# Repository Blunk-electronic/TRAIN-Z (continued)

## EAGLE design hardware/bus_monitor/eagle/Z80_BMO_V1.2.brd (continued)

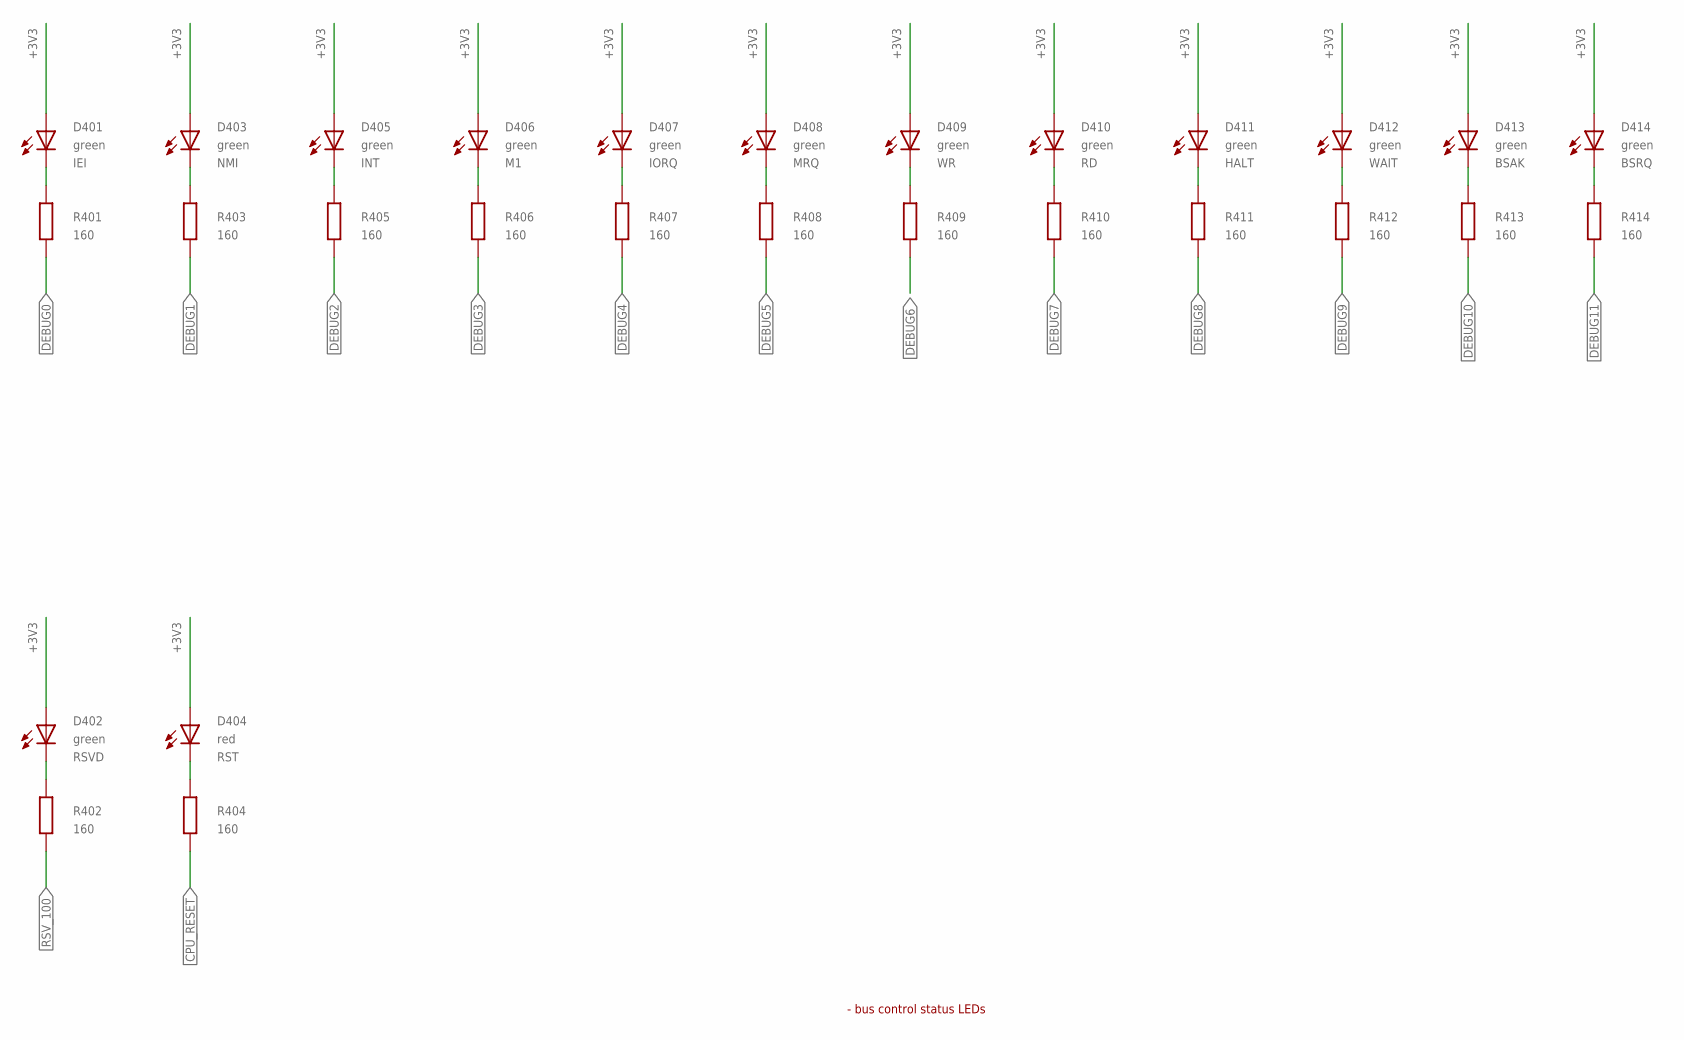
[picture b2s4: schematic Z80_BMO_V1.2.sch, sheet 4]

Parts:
D401, D402, D403, D405, D406, D407, D408, D409, D410, D411, D412, D413, D414: green; T_LED_3MM; PART_CODE_BEL LED_PAC_T_3mm_VAL_green
D404: red; T_LED_3MM; PART_CODE_BEL LED_PAC_T_3mm_VAL_red
R401, R402, R403, R404, R405, R406, R407, R408, R409, R410, R411, R412, R413, R414: 160; T_0207_GRID10MM; PART_CODE_BEL R_PAC_T_0207_GRID10mm_VAL_160

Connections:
!CPU_RESET: R404.2; also elsewhere on the board
+3V3: D401.A, D402.A, D403.A, D404.A, D405.A, D406.A, D407.A, D408.A, D409.A, D410.A, D411.A, D412.A, D413.A, D414.A; also elsewhere on the board
DEBUG0: R401.2; also elsewhere on the board
DEBUG0_LED: D401.C, R401.1
DEBUG1: R403.2; also elsewhere on the board
DEBUG1_LED: D403.C, R403.1
DEBUG2: R405.2; also elsewhere on the board
DEBUG2_LED: D405.C, R405.1
DEBUG3: R406.2; also elsewhere on the board
DEBUG3_LED: D406.C, R406.1
DEBUG4: R407.2; also elsewhere on the board
DEBUG4_LED: D407.C, R407.1
DEBUG5: R408.2; also elsewhere on the board
DEBUG5_LED: D408.C, R408.1
DEBUG6: R409.2; also elsewhere on the board
DEBUG6_LED: D409.C, R409.1
DEBUG7: R410.2; also elsewhere on the board
DEBUG7_LED: D410.C, R410.1
DEBUG8: R411.2; also elsewhere on the board
DEBUG8_LED: D411.C, R411.1
DEBUG9: R412.2; also elsewhere on the board
DEBUG9_LED: D412.C, R412.1
DEBUG10: R413.2; also elsewhere on the board
DEBUG10_LED: D413.C, R413.1
DEBUG11: R414.2; also elsewhere on the board
DEBUG11_LED: D414.C, R414.1
RST_LED_C: D404.C, R404.1
RSV_100: R402.2; also elsewhere on the board
RSV_100_LED: D402.C, R402.1

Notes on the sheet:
- bus control status LEDs

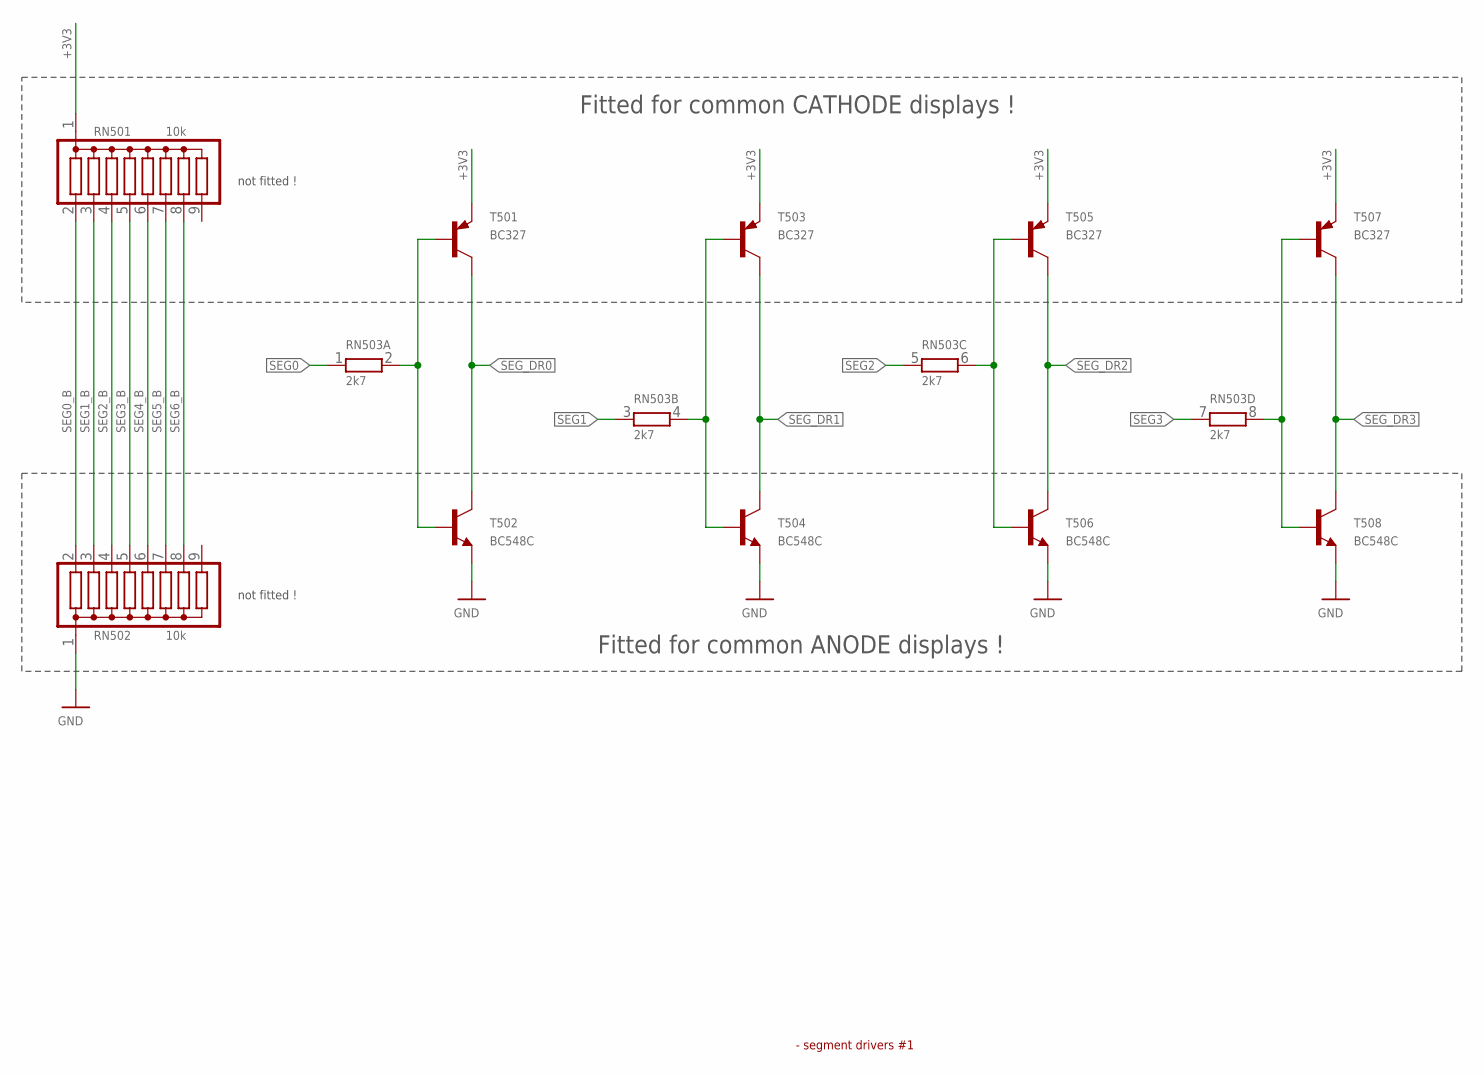
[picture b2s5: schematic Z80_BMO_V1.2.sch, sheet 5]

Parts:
RN501, RN502: 10k; T_SIL9; PART_CODE_BEL RN_PAC_T_SIL9_VAL_10k
RN503: 2k7; T_SIL8; PART_CODE_BEL RN_PAC_T_SIL8_VAL_2k7
T501, T503, T505, T507: BC327; T_TO92-CBE; PART_CODE_BEL T_PAC_T_TO92-CBE_VAL_BC327
T502, T504, T506, T508: BC548C; T_TO92-CBE; PART_CODE_BEL T_PAC_T_TO92-CBE_VAL_BC548C

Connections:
+3V3: RN501.1, T501.E, T503.E, T505.E, T507.E; also elsewhere on the board
GND: RN502.1, T502.E, T504.E, T506.E, T508.E; also elsewhere on the board
SEG0: RN503.1; also elsewhere on the board
SEG0_B: RN501.2, RN502.2, RN503.2, T501.B, T502.B
SEG1: RN503.3 (1); also elsewhere on the board
SEG1_B: RN501.3, RN502.3, RN503.4 (2), T503.B, T504.B
SEG2: RN503.5 (1); also elsewhere on the board
SEG2_B: RN501.4, RN502.4, RN503.6 (2), T505.B, T506.B
SEG3: RN503.7 (1); also elsewhere on the board
SEG3_B: RN501.5, RN502.5, RN503.8 (2), T507.B, T508.B
SEG4_B: RN501.6, RN502.6; also elsewhere on the board
SEG5_B: RN501.7, RN502.7; also elsewhere on the board
SEG6_B: RN501.8, RN502.8; also elsewhere on the board
SEG_DR0: T501.C, T502.C; also elsewhere on the board
SEG_DR1: T503.C, T504.C; also elsewhere on the board
SEG_DR2: T505.C, T506.C; also elsewhere on the board
SEG_DR3: T507.C, T508.C; also elsewhere on the board

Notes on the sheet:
Fitted for common ANODE displays !
Fitted for common CATHODE displays !
not fitted !
- segment drivers #1

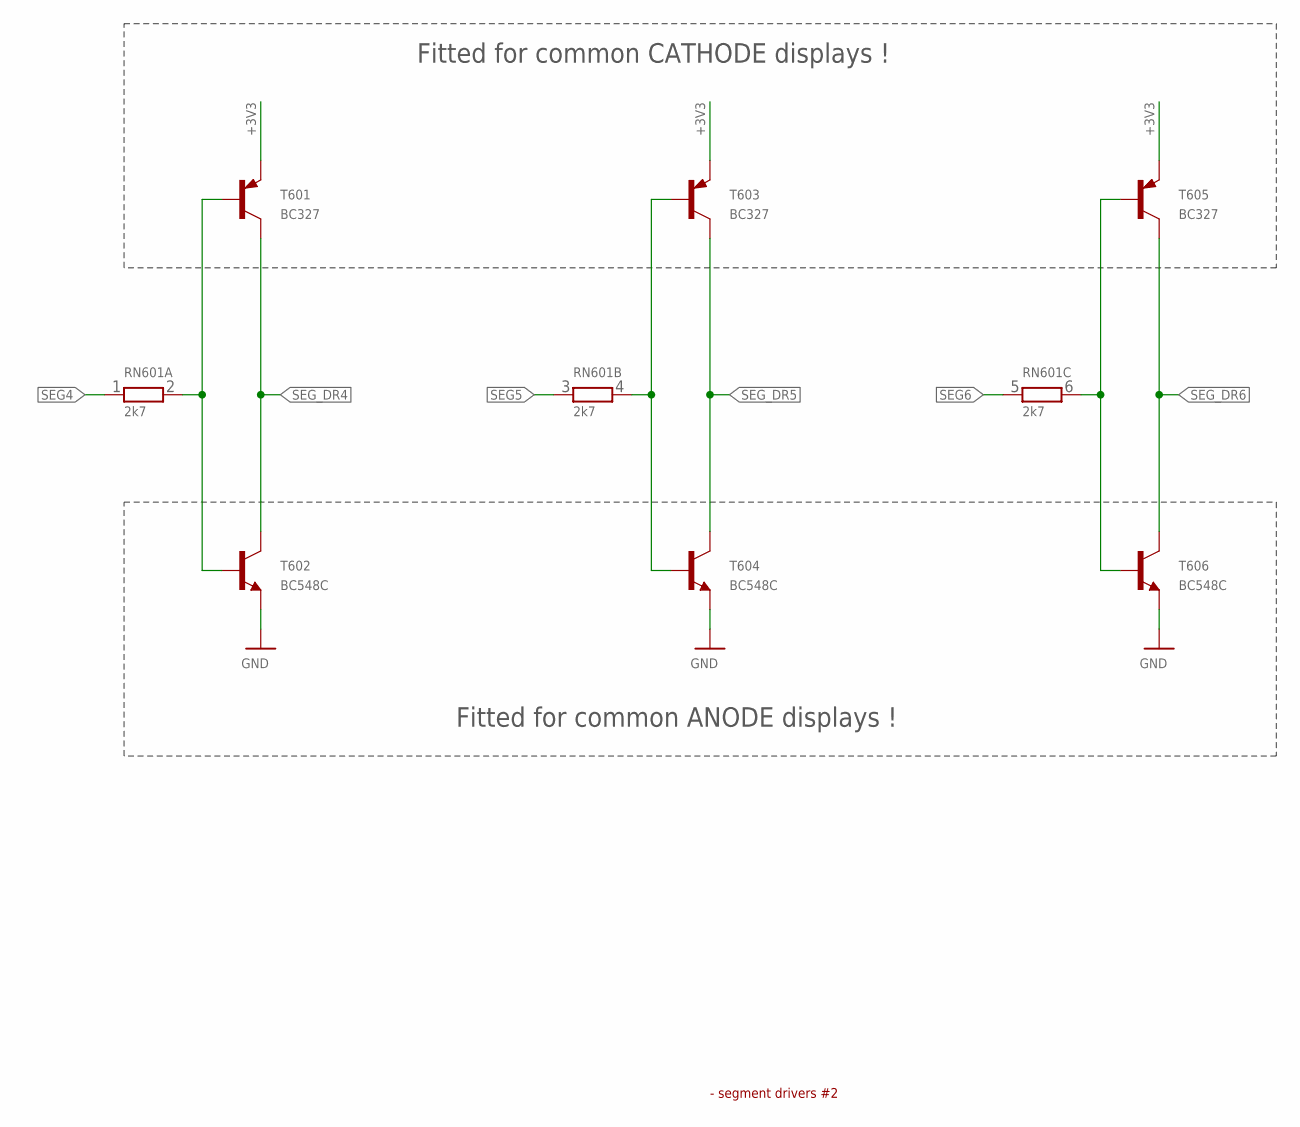
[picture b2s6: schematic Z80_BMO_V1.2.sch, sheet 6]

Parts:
RN601: 2k7; T_SIL8; PART_CODE_BEL RN_PAC_T_SIL8_VAL_2k7
T601, T603, T605: BC327; T_TO92-CBE; PART_CODE_BEL T_PAC_T_TO92-CBE_VAL_BC327
T602, T604, T606: BC548C; T_TO92-CBE; PART_CODE_BEL T_PAC_T_TO92-CBE_VAL_BC548C

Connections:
+3V3: T601.E, T603.E, T605.E; also elsewhere on the board
GND: T602.E, T604.E, T606.E; also elsewhere on the board
SEG4: RN601.1; also elsewhere on the board
SEG4_B: RN601.2, T601.B, T602.B; also elsewhere on the board
SEG5: RN601.3 (1); also elsewhere on the board
SEG5_B: RN601.4 (2), T603.B, T604.B; also elsewhere on the board
SEG6: RN601.5 (1); also elsewhere on the board
SEG6_B: RN601.6 (2), T605.B, T606.B; also elsewhere on the board
SEG_DR4: T601.C, T602.C; also elsewhere on the board
SEG_DR5: T603.C, T604.C; also elsewhere on the board
SEG_DR6: T605.C, T606.C; also elsewhere on the board

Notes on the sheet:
Fitted for common ANODE displays !
Fitted for common CATHODE displays !
- segment drivers #2

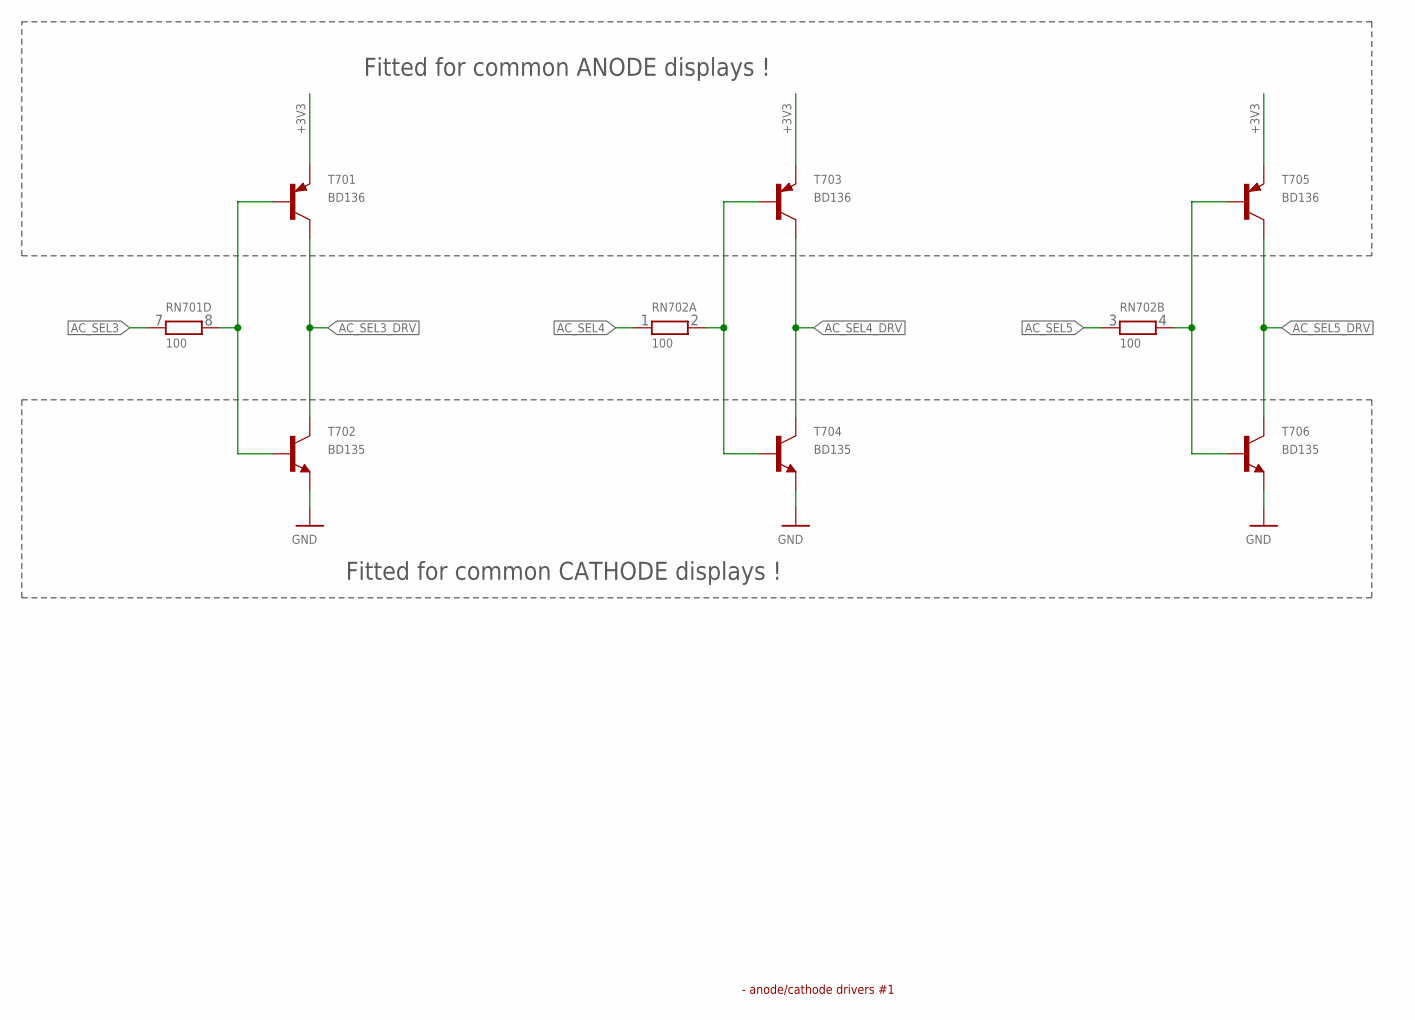
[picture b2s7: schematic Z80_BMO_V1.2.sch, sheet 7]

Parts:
RN701, RN702: 100; T_SIL8; PART_CODE_BEL RN_PAC_T_SIL8_VAL_100
T701, T703, T705: BD136; T_TO126_VERTICAL; PART_CODE_BEL T_PAC_T_TO126_VERTICAL_VAL_BD136
T702, T704, T706: BD135; T_TO126_VERTICAL; PART_CODE_BEL T_PAC_T_TO126_VERTICAL_VAL_BD135

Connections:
+3V3: T701.E, T703.E, T705.E; also elsewhere on the board
AC_SEL3: RN701.7 (1); also elsewhere on the board
AC_SEL3_DRV: T701.C, T702.C; also elsewhere on the board
AC_SEL4: RN702.1; also elsewhere on the board
AC_SEL4_DRV: T703.C, T704.C; also elsewhere on the board
AC_SEL5: RN702.3 (1); also elsewhere on the board
AC_SEL5_DRV: T705.C, T706.C; also elsewhere on the board
AC_SEL_B3: RN701.8 (2), T701.B, T702.B; also elsewhere on the board
AC_SEL_B4: RN702.2, T703.B, T704.B; also elsewhere on the board
AC_SEL_B5: RN702.4 (2), T705.B, T706.B; also elsewhere on the board
GND: T702.E, T704.E, T706.E; also elsewhere on the board

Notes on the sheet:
Fitted for common ANODE displays !
Fitted for common CATHODE displays !
- anode/cathode drivers #1

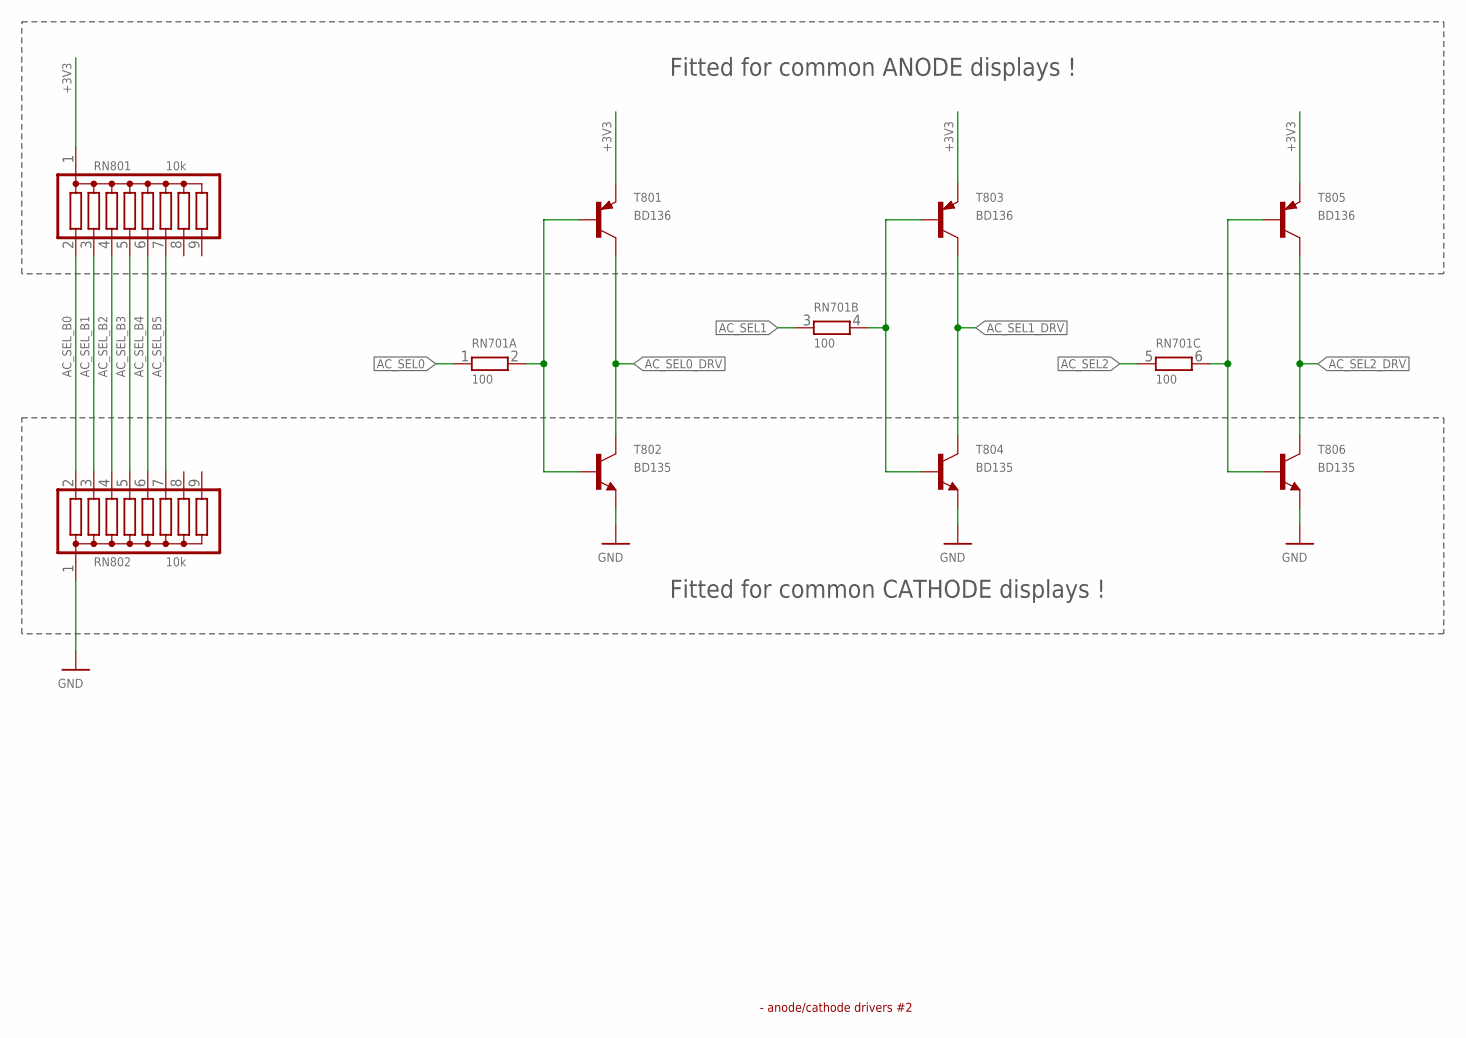
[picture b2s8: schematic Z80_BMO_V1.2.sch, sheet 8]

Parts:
RN701: 100; T_SIL8; PART_CODE_BEL RN_PAC_T_SIL8_VAL_100
RN801, RN802: 10k; T_SIL9; PART_CODE_BEL RN_PAC_T_SIL9_VAL_10k
T801, T803, T805: BD136; T_TO126_VERTICAL; PART_CODE_BEL T_PAC_T_TO126_VERTICAL_VAL_BD136
T802, T804, T806: BD135; T_TO126_VERTICAL; PART_CODE_BEL T_PAC_T_TO126_VERTICAL_VAL_BD135

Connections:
+3V3: RN801.1, T801.E, T803.E, T805.E; also elsewhere on the board
AC_SEL0: RN701.1; also elsewhere on the board
AC_SEL0_DRV: T801.C, T802.C; also elsewhere on the board
AC_SEL1: RN701.3 (1); also elsewhere on the board
AC_SEL1_DRV: T803.C, T804.C; also elsewhere on the board
AC_SEL2: RN701.5 (1); also elsewhere on the board
AC_SEL2_DRV: T805.C, T806.C; also elsewhere on the board
AC_SEL_B0: RN701.2, RN801.2, RN802.2, T801.B, T802.B
AC_SEL_B1: RN701.4 (2), RN801.3, RN802.3, T803.B, T804.B
AC_SEL_B2: RN701.6 (2), RN801.4, RN802.4, T805.B, T806.B
AC_SEL_B3: RN801.5, RN802.5; also elsewhere on the board
AC_SEL_B4: RN801.6, RN802.6; also elsewhere on the board
AC_SEL_B5: RN801.7, RN802.7; also elsewhere on the board
GND: RN802.1, T802.E, T804.E, T806.E; also elsewhere on the board

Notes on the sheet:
Fitted for common ANODE displays !
Fitted for common CATHODE displays !
- anode/cathode drivers #2

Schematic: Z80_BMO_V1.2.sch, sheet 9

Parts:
RN901, RN902, RN903: 10k; T_SIL9; PART_CODE_BEL RN_PAC_T_SIL9_VAL_10k
S901, S902, S903: PUSH_BUTTON_T_6X6MM; T_PUSH_BUTTON_6X6
S904: DIP08; T_DIP08
TP901: TEST_POINT_T_SMALL; T_TEST_POINT_SMALL
X901: MALE_2X20-T-VERTICAL; T_MALE_2X20_VERTICAL

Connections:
!CPU_RESET: X901.40; also elsewhere on the board
+3V3: RN901.1, RN902.1, RN903.1, X901.1, X901.3, X901.5; also elsewhere on the board
DEBUG0: RN903.2, S904.4, X901.18; also elsewhere on the board
DEBUG1: RN903.3, S904.5, X901.24; also elsewhere on the board
DEBUG2: RN903.4, S904.6, X901.26; also elsewhere on the board
DEBUG3: RN903.5, X901.28; also elsewhere on the board
DEBUG4: RN903.6, X901.30; also elsewhere on the board
DEBUG5: RN903.7, X901.36; also elsewhere on the board
DEBUG6: RN903.8; also elsewhere on the board
DEBUG7: RN903.9; also elsewhere on the board
GND: S901.2 (B1), S901.4 (B1), S902.2 (B1), S902.4 (B1), S903.2 (B1), S903.4 (B1), S904.9, S904.10, S904.11, S904.12, S904.13, S904.14, S904.15, S904.16, X901.9, X901.11, X901.13, X901.15, X901.17, X901.19, X901.21, X901.23, X901.25, X901.27, X901.29, X901.31, X901.33, X901.35, X901.37, X901.39; also elsewhere on the board
PIO0: RN902.6, X901.2; also elsewhere on the board
PIO1: RN902.5, X901.4; also elsewhere on the board
PIO2: RN902.2, X901.6; also elsewhere on the board
PIO3: RN902.3, X901.8; also elsewhere on the board
PIO4: RN902.4, X901.10; also elsewhere on the board
PIO5: RN902.7, X901.12; also elsewhere on the board
PIO6: RN902.8, X901.14; also elsewhere on the board
PIO7: RN902.9, X901.16; also elsewhere on the board
RSV_100: RN901.7, TP901.1, X901.38; also elsewhere on the board
RSV_300: RN901.6, S904.7; also elsewhere on the board
RSV_GCK2: RN901.5, S904.8; also elsewhere on the board
ST_IN0: RN901.8, X901.20; also elsewhere on the board
ST_IN1: RN901.9, X901.22; also elsewhere on the board
ST_OUT0: X901.32; also elsewhere on the board
ST_OUT1: X901.34; also elsewhere on the board
SWITCH0: RN901.2, S903.1 (A1), S903.3 (A1), S904.1; also elsewhere on the board
SWITCH1: RN901.3, S902.1 (A1), S902.3 (A1), S904.2; also elsewhere on the board
SWITCH2: RN901.4, S901.1 (A1), S901.3 (A1), S904.3; also elsewhere on the board

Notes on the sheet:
- DBG & PIO connectos - switches & buttons

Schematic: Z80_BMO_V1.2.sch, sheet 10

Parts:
J1001: JUMPER_1X2-T-VERTICAL; T_MALE_2X1_VERTICAL
R1001, R1002: 300; T_0207_GRID10MM; PART_CODE_BEL R_PAC_T_0207_GRID10mm_VAL_300
RN1001: 10k; T_SIL9; PART_CODE_BEL RN_PAC_T_SIL9_VAL_10k
TP1001, TP1002, TP1003, TP1004: TEST_POINT_T_SMALL; T_TEST_POINT_SMALL
X1001: MALE_2X5-T-VERTICAL_2.54MM; T_MALE_2X5_VERTICAL

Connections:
+3V3: J1001.1, RN1001.1; also elsewhere on the board
GND: R1001.2, R1002.2, X1001.2, X1001.4, X1001.6, X1001.8; also elsewhere on the board
TCK: R1001.1, TP1001.1, X1001.1; also elsewhere on the board
TDI: RN1001.3, TP1004.1, X1001.7; also elsewhere on the board
TDO: RN1001.4, TP1003.1, X1001.5; also elsewhere on the board
TMS: R1002.1, TP1002.1, X1001.3; also elsewhere on the board
VREF_JTAG: J1001.2, X1001.10

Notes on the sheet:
- JTAG
CAUTION: CLOSE JUMPER IF JTAG EQUIPMENT REQUIRES VREF ! OTHERWISE LEAVE OPEN TO PREVENT DAMAGE !

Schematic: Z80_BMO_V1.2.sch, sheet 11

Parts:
R1101: 2k7; T_0207_GRID10MM; PART_CODE_BEL R_PAC_T_0207_GRID10mm_VAL_2k7
R1102: 10k; T_0207_GRID10MM; PART_CODE_BEL R_PAC_T_0207_GRID10mm_VAL_10k
R1103, R1104: 300; T_0207_GRID10MM; PART_CODE_BEL R_PAC_T_0207_GRID10mm_VAL_300
T1101: BC548C; T_TO92-CBE; PART_CODE_BEL T_PAC_T_TO92-CBE_VAL_BC548C
TP1101, TP1102, TP1103: TEST_POINT_T_SMALL; T_TEST_POINT_SMALL
X1101, X1102, X1103, X1104: MALE_2X20-T-VERTICAL; T_MALE_2X20_VERTICAL

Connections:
!CPU_BUSACK: X1101.38; also elsewhere on the board
!CPU_BUSREQ: X1101.36; also elsewhere on the board
!CPU_HALT: X1101.32; also elsewhere on the board
!CPU_INT: X1102.36; also elsewhere on the board
!CPU_IOREQ: X1101.24; also elsewhere on the board
!CPU_M1: X1101.20; also elsewhere on the board
!CPU_MREQ: X1101.22; also elsewhere on the board
!CPU_NMI: X1102.38; also elsewhere on the board
!CPU_RD: X1101.26; also elsewhere on the board
!CPU_RESET: R1103.2, T1101.C, TP1101.1, TP1102.1, X1102.40; also elsewhere on the board
!CPU_RFSH: X1101.30; also elsewhere on the board
!CPU_WAIT: X1101.34; also elsewhere on the board
!CPU_WR: X1101.28; also elsewhere on the board
!EX_BUSAK: X1103.38; also elsewhere on the board
!EX_BUSREQ: X1103.36; also elsewhere on the board
!EX_HALT: X1103.32; also elsewhere on the board
!EX_INT: X1104.36; also elsewhere on the board
!EX_IOREQ: X1103.24; also elsewhere on the board
!EX_M1: X1103.20; also elsewhere on the board
!EX_MREQ: X1103.22; also elsewhere on the board
!EX_NMI: X1104.38; also elsewhere on the board
!EX_RD: X1103.26; also elsewhere on the board
!EX_RESET: R1104.2, TP1103.1, X1104.40; also elsewhere on the board
!EX_RFSH: X1103.30; also elsewhere on the board
!EX_WAIT: X1103.34; also elsewhere on the board
!EX_WR: X1103.28; also elsewhere on the board
+3V3: R1103.1, R1104.1; also elsewhere on the board
A0: X1102.2; also elsewhere on the board
A1: X1102.4; also elsewhere on the board
A2: X1102.6; also elsewhere on the board
A3: X1102.8; also elsewhere on the board
A4: X1102.10; also elsewhere on the board
A5: X1102.12; also elsewhere on the board
A6: X1102.14; also elsewhere on the board
A7: X1102.16; also elsewhere on the board
A8: X1102.18; also elsewhere on the board
A9: X1102.20; also elsewhere on the board
A10: X1102.22; also elsewhere on the board
A11: X1102.24; also elsewhere on the board
A12: X1102.26; also elsewhere on the board
A13: X1102.28; also elsewhere on the board
A14: X1102.30; also elsewhere on the board
A15: X1102.32; also elsewhere on the board
A_EX0: X1104.2; also elsewhere on the board
A_EX1: X1104.4; also elsewhere on the board
A_EX2: X1104.6; also elsewhere on the board
A_EX3: X1104.8; also elsewhere on the board
A_EX4: X1104.10; also elsewhere on the board
A_EX5: X1104.12; also elsewhere on the board
A_EX6: X1104.14; also elsewhere on the board
A_EX7: X1104.16; also elsewhere on the board
A_EX8: X1104.18; also elsewhere on the board
A_EX9: X1104.20; also elsewhere on the board
A_EX10: X1104.22; also elsewhere on the board
A_EX11: X1104.24; also elsewhere on the board
A_EX12: X1104.26; also elsewhere on the board
A_EX13: X1104.28; also elsewhere on the board
A_EX14: X1104.30; also elsewhere on the board
A_EX15: X1104.32; also elsewhere on the board
CPU_CLK: X1101.40; also elsewhere on the board
CPU_RESET: R1101.2; also elsewhere on the board
CPU_RESET_B: R1101.1, R1102.1, T1101.B
CPU_RSV0: X1101.18
D0: X1101.2; also elsewhere on the board
D1: X1101.4; also elsewhere on the board
D2: X1101.6; also elsewhere on the board
D3: X1101.8; also elsewhere on the board
D4: X1101.10; also elsewhere on the board
D5: X1101.12; also elsewhere on the board
D6: X1101.14; also elsewhere on the board
D7: X1101.16; also elsewhere on the board
D_EX0: X1103.2; also elsewhere on the board
D_EX1: X1103.4; also elsewhere on the board
D_EX2: X1103.6; also elsewhere on the board
D_EX3: X1103.8; also elsewhere on the board
D_EX4: X1103.10; also elsewhere on the board
D_EX5: X1103.12; also elsewhere on the board
D_EX6: X1103.14; also elsewhere on the board
D_EX7: X1103.16; also elsewhere on the board
EXT_IEI: X1104.34; also elsewhere on the board
EX_CLK: X1103.40; also elsewhere on the board
GND: R1102.2, T1101.E, X1101.1, X1101.3, X1101.5, X1101.7, X1101.9, X1101.11, X1101.13, X1101.15, X1101.17, X1101.19, X1101.21, X1101.23, X1101.25, X1101.27, X1101.29, X1101.31, X1101.33, X1101.35, X1101.37, X1101.39, X1102.1, X1102.3, X1102.5, X1102.7, X1102.9, X1102.11, X1102.13, X1102.15, X1102.17, X1102.19, X1102.21, X1102.23, X1102.25, X1102.27, X1102.29, X1102.31, X1102.33, X1102.35, X1102.37, X1102.39, X1103.1, X1103.3, X1103.5, X1103.7, X1103.9, X1103.11, X1103.13, X1103.15, X1103.17, X1103.19, X1103.21, X1103.23, X1103.25, X1103.27, X1103.29, X1103.31, X1103.33, X1103.35, X1103.37, X1103.39, X1104.1, X1104.3, X1104.5, X1104.7, X1104.9, X1104.11, X1104.13, X1104.15, X1104.17, X1104.19, X1104.21, X1104.23, X1104.25, X1104.27, X1104.29, X1104.31, X1104.33, X1104.35, X1104.37, X1104.39; also elsewhere on the board
IEI: X1102.34; also elsewhere on the board

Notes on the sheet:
- bus connectors - reset

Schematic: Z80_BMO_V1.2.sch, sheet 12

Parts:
C1201: 4n7; T_7X3MM_GRID_5MM; PART_CODE_BEL C_PAC_T_7x3mm_GRID_5mm_VAL_4n7
C1202: 100n; S_0805; PART_CODE_BEL C_PAC_S_0805_VAL_100n
IC1201: 4093N; T_NDIP14
R1201: 10k; T_0207_GRID10MM; PART_CODE_BEL R_PAC_T_0207_GRID10mm_VAL_10k
TP1201, TP1202, TP1203, TP1204, TP1205: TEST_POINT_T_SMALL; T_TEST_POINT_SMALL

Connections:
+3V3: C1202.1, IC1201.14 (VCC); also elsewhere on the board
CLK_OSC: IC1201.3 (O), TP1201.1; also elsewhere on the board
CLK_SLOW: IC1201.1 (I0), IC1201.2 (I1), IC1201.4 (O), R1201.1
GND: C1201.2, C1202.2, IC1201.7 (GND); also elsewhere on the board
unnamed: C1201.1, IC1201.5 (I0), IC1201.6 (I1), R1201.2
ST_IN0: IC1201.8 (I0), IC1201.9 (I1), TP1204.1; also elsewhere on the board
ST_IN1: IC1201.12 (I0), IC1201.13 (I1), TP1205.1; also elsewhere on the board
ST_OUT0: IC1201.10 (O), TP1202.1; also elsewhere on the board
ST_OUT1: IC1201.11 (O), TP1203.1; also elsewhere on the board

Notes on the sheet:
- Oscillator - Schmitt-Triggers
45 kHz

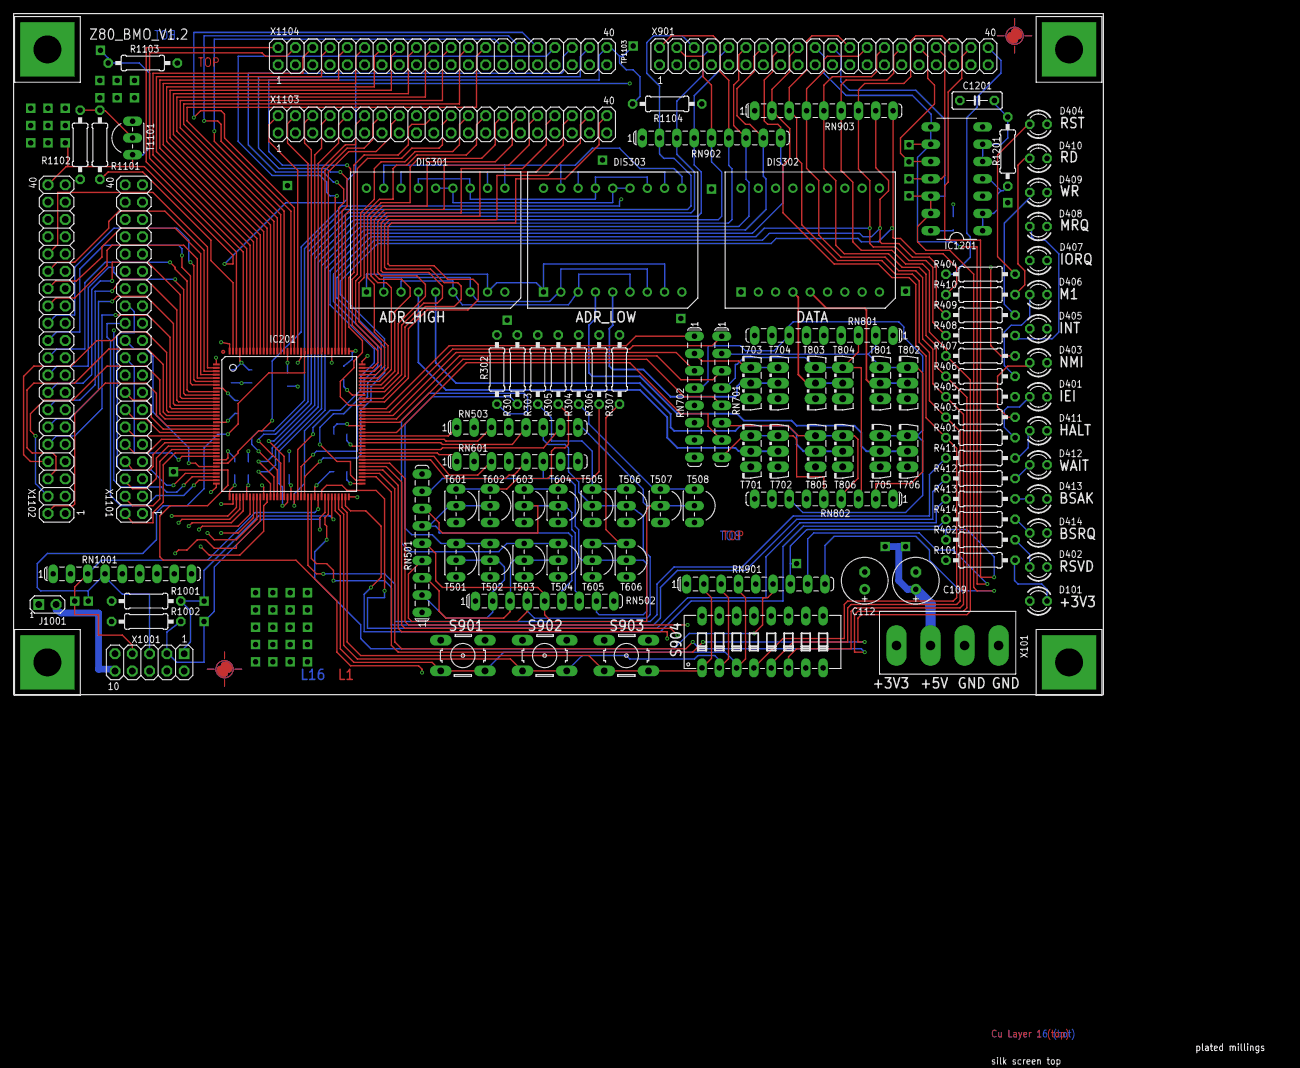
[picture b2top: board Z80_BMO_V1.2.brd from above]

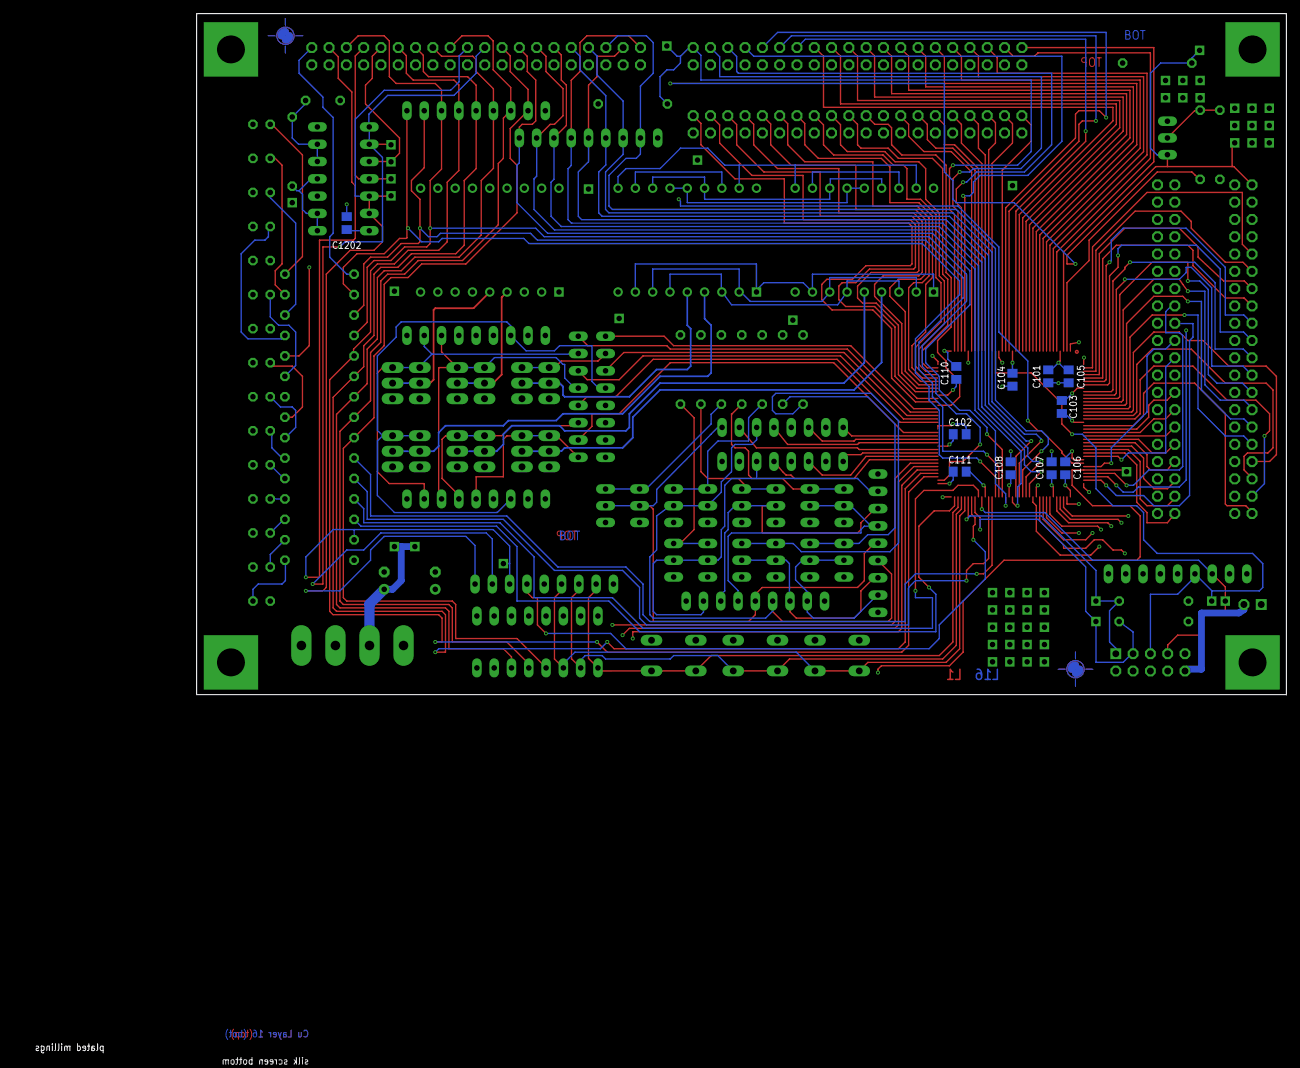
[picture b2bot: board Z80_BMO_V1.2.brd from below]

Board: 4 copper layers, 160.0 x 100.0 mm, 178 parts (11 on the bottom side), 188 nets.

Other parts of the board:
DRILEGEND: DRILEGEND
U$1: A4_LANDSCAPE

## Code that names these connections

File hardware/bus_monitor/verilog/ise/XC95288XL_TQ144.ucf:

#2012-07-05
#V1.0

NET "A_CPU<15>"       LOC =  "S:PIN2";
NET "A_CPU<14>"       LOC =  "S:PIN3";
NET "A_CPU<13>"       LOC =  "S:PIN4";
NET "A_CPU<12>"       LOC =  "S:PIN5";
NET "A_CPU<11>"       LOC =  "S:PIN6";
NET "A_CPU<10>"       LOC =  "S:PIN7";
NET "A_CPU<9>"       LOC =  "S:PIN9";
NET "A_CPU<8>"       LOC =  "S:PIN10";
NET "A_CPU<7>"       LOC =  "S:PIN11";
NET "A_CPU<6>"       LOC =  "S:PIN12";
NET "A_CPU<5>"      LOC =  "S:PIN13";
NET "A_CPU<4>"      LOC =  "S:PIN14";
NET "A_CPU<3>"      LOC =  "S:PIN15";
NET "A_CPU<2>"      LOC =  "S:PIN16";
NET "A_CPU<1>"      LOC =  "S:PIN17";
NET "A_CPU<0>"      LOC =  "S:PIN19";

NET "D_CPU<7>"       LOC =  "S:PIN20";
NET "D_CPU<6>"       LOC =  "S:PIN21";
NET "D_CPU<5>"       LOC =  "S:PIN22";
NET "D_CPU<4>"       LOC =  "S:PIN23";
NET "D_CPU<3>"       LOC =  "S:PIN24";
NET "D_CPU<2>"       LOC =  "S:PIN25";
NET "D_CPU<1>"       LOC =  "S:PIN26";
NET "D_CPU<0>"       LOC =  "S:PIN27";

NET "BUS_ACK_CPU"    LOC =  "S:PIN45";
NET "BUS_REQ_CPU"    LOC =  "S:PIN43";
NET "NMI_CPU"        LOC =  "S:PIN48";
NET "INT_CPU"        LOC =  "S:PIN44";

NET "CLK_CPU"        LOC =  "S:PIN38";
NET "CLK_OSC"        LOC =  "S:PIN30";
NET "RSV_GCK2"			LOC =	 "S:PIN32";

NET "HALT_CPU"       LOC =  "S:PIN40";
NET "IEI_CPU"        LOC =  "S:PIN46";
NET "IO_REQ_CPU"     LOC =  "S:PIN35";
NET "M1_CPU"         LOC =  "S:PIN28";
NET "MEM_REQ_CPU"    LOC =  "S:PIN31";

NET "RD_CPU"         LOC =  "S:PIN33";
NET "WR_CPU"         LOC =  "S:PIN34";
NET "RESET_CPU"      LOC =  "S:PIN143";
NET "RFSH_CPU"       LOC =  "S:PIN39";
NET "WAIT_CPU"       LOC =  "S:PIN41";
#fertich

NET "A_EX<0>"        LOC =  "S:PIN142";
NET "A_EX<10>"       LOC =  "S:PIN131";
NET "A_EX<11>"       LOC =  "S:PIN130";
NET "A_EX<12>"       LOC =  "S:PIN129";
NET "A_EX<13>"       LOC =  "S:PIN128";
NET "A_EX<14>"       LOC =  "S:PIN126";
NET "A_EX<15>"       LOC =  "S:PIN125";
NET "A_EX<1>"        LOC =  "S:PIN140";
NET "A_EX<2>"        LOC =  "S:PIN139";
NET "A_EX<3>"        LOC =  "S:PIN138";
NET "A_EX<4>"        LOC =  "S:PIN137";
NET "A_EX<5>"        LOC =  "S:PIN136";
NET "A_EX<6>"        LOC =  "S:PIN135";
NET "A_EX<7>"        LOC =  "S:PIN134";
NET "A_EX<8>"        LOC =  "S:PIN133";
NET "A_EX<9>"        LOC =  "S:PIN132";

NET "D_EX<0>"        LOC =  "S:PIN124";
NET "D_EX<1>"        LOC =  "S:PIN121";
NET "D_EX<2>"        LOC =  "S:PIN120";
NET "D_EX<3>"        LOC =  "S:PIN119";
NET "D_EX<4>"        LOC =  "S:PIN118";
NET "D_EX<5>"        LOC =  "S:PIN117";
NET "D_EX<6>"        LOC =  "S:PIN116";
NET "D_EX<7>"        LOC =  "S:PIN115";

NET "BUS_ACK_EX"     LOC =  "S:PIN98";
NET "CLK_EX"         LOC =  "S:PIN97";
NET "WAIT_EX"        LOC =  "S:PIN101";
NET "NMI_EX"         LOC =  "S:PIN111";
NET "INT_EX"         LOC =  "S:PIN112";
NET "BUS_REQ_EX"     LOC =  "S:PIN100";
NET "HALT_EX"        LOC =  "S:PIN102";
NET "IEI_EX"         LOC =  "S:PIN113";
NET "IO_REQ_EX"      LOC =  "S:PIN106";
NET "M1_EX"          LOC =  "S:PIN96";
NET "MEM_REQ_EX"     LOC =  "S:PIN107";
NET "RD_EX"          LOC =  "S:PIN105";
NET "WR_EX"          LOC =  "S:PIN104";
NET "RESET_EX"       LOC =  "S:PIN110";
NET "RFSH_EX"        LOC =  "S:PIN103";

NET "DEBUG_0"        LOC =  "S:PIN79";
NET "DEBUG_1"        LOC =  "S:PIN78";
NET "DEBUG_2"        LOC =  "S:PIN77";
NET "DEBUG_3"        LOC =  "S:PIN76";
NET "DEBUG_4"        LOC =  "S:PIN75";
NET "DEBUG_5"        LOC =  "S:PIN74";
NET "DEBUG_6"        LOC =  "S:PIN58";
NET "DEBUG_7"        LOC =  "S:PIN59";
NET "DEBUG_8"        LOC =  "S:PIN60";
NET "DEBUG_9"        LOC =  "S:PIN61";
NET "DEBUG_10"       LOC =  "S:PIN64";
NET "DEBUG_11"       LOC =  "S:PIN71";

NET "SEG_OUT<0>"     LOC =  "S:PIN87";
NET "SEG_OUT<1>"     LOC =  "S:PIN86";
NET "SEG_OUT<2>"     LOC =  "S:PIN85";
NET "SEG_OUT<3>"     LOC =  "S:PIN83";
NET "SEG_OUT<4>"     LOC =  "S:PIN82";
NET "SEG_OUT<5>"     LOC =  "S:PIN81";
NET "SEG_OUT<6>"     LOC =  "S:PIN80";

NET "AC_SEL<0>"      LOC =  "S:PIN94";
NET "AC_SEL<1>"      LOC =  "S:PIN92";
NET "AC_SEL<2>"      LOC =  "S:PIN91";
NET "AC_SEL<3>"      LOC =  "S:PIN88";
NET "AC_SEL<4>"      LOC =  "S:PIN95";
NET "AC_SEL<5>"      LOC =  "S:PIN93";

NET "PIO<0>"         LOC =  "S:PIN49";
NET "PIO<1>"         LOC =  "S:PIN50";
NET "PIO<2>"         LOC =  "S:PIN51";
NET "PIO<3>"         LOC =  "S:PIN52";
NET "PIO<4>"         LOC =  "S:PIN53";
NET "PIO<5>"         LOC =  "S:PIN54";
NET "PIO<6>"         LOC =  "S:PIN56";
NET "PIO<7>"         LOC =  "S:PIN57";

NET "SWITCH<0>"      LOC =  "S:PIN70";
NET "SWITCH<1>"      LOC =  "S:PIN69";
NET "SWITCH<2>"      LOC =  "S:PIN68";
NET "rsv_300"      	LOC =  "S:PIN66";

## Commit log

2015-09-25 this is my first commit
2015-09-25 these are the eagle design files
2015-09-26 added firmware files
2015-09-26 added further firmware files
2015-09-26 added documentation
2015-09-27 cleaned up a lot
2015-09-27 ordered pdf files
2015-10-02 updated readme file
2015-10-22 updated manual
2019-09-14 files for systest
